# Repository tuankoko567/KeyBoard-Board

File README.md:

# KeyBoard-Board
 A fully custom 4 layers mechanical keyboard PCB based on the RP2040 microcontroller

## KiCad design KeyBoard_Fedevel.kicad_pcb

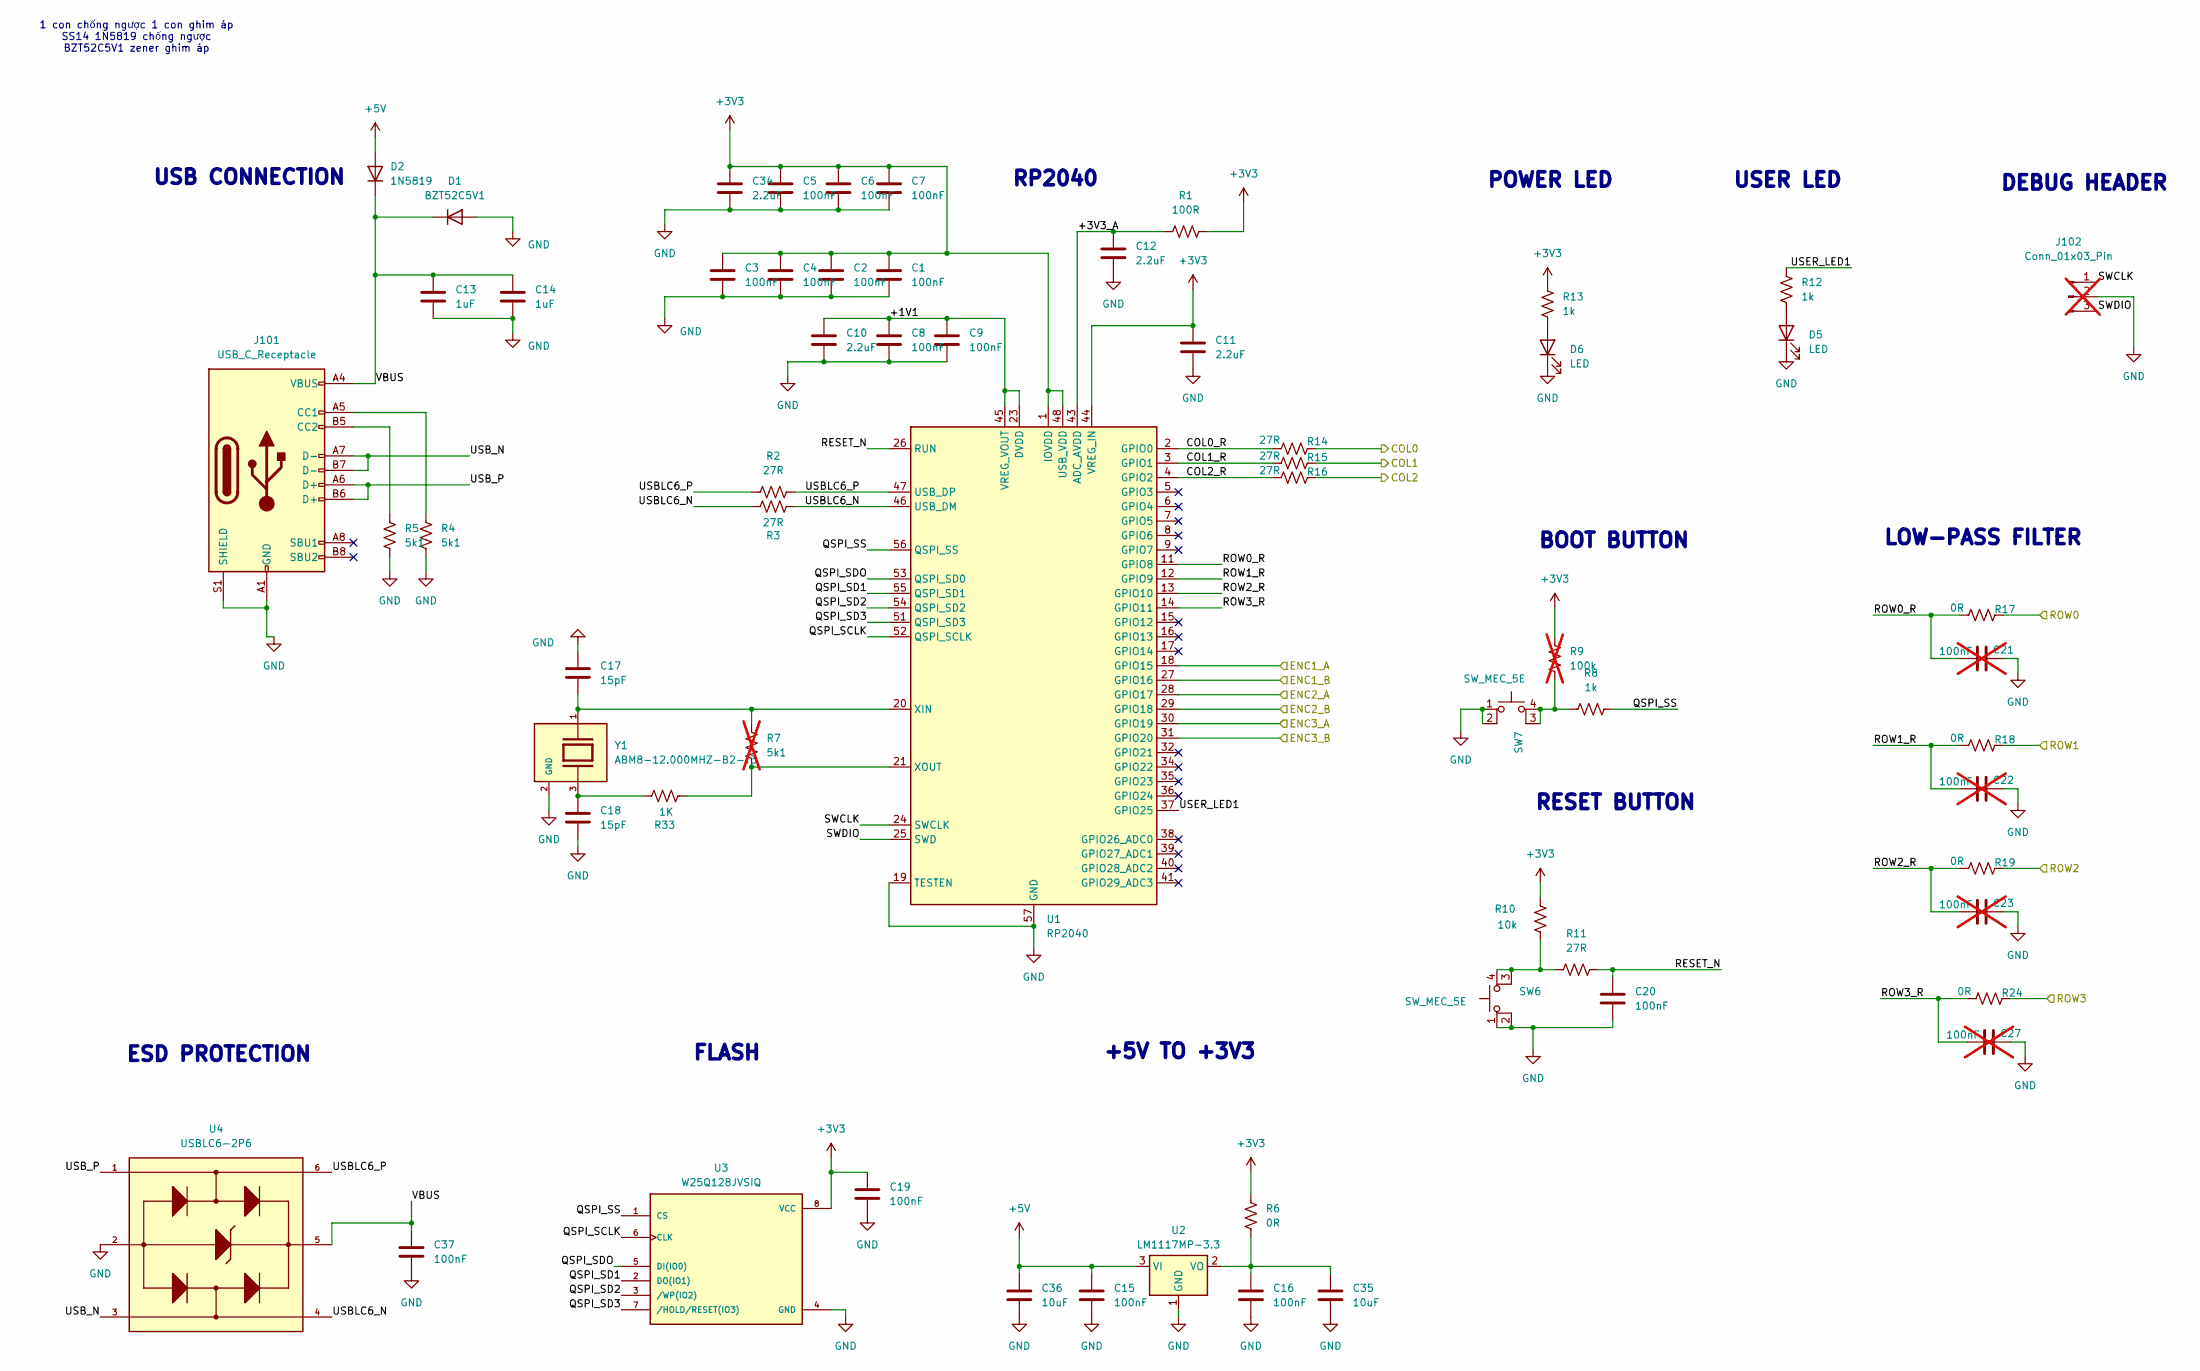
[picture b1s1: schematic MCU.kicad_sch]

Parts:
C1, C2, C3, C4, C5, C6, C7, C8, C9, C15, C16, C19, C20, C37: 100nF; C_0603
C10, C11, C12, C34: 2.2uF; C_0603
C13, C14: 1uF; C_0603
C17, C18: 15pF; C_0603
C21, C22, C23, C27: 100nF; C_0603; not fitted
C35, C36: 10uF; C_0603
D1: BZT52C5V1; Package-Diode-D_SOD_123
D2: 1N5819; D_SMA
D5, D6: LED; LED_0805
J101: USB_C_Receptacle; USB_C_Receptacle_XKB_U262-16XN-4BVC11
J102: Conn_01x03_Pin; PinHeader_1x03_P2.54mm_Vertical; not fitted
R1: 100R; R_0603
R2, R3, R11, R14, R15, R16: 27R; R_0603
R4, R5: 5k1; R_0603
R6, R17, R18, R19, R24: 0R; R_0603
R7: 5k1; R_0603; not fitted
R8, R12, R13: 1k; R_0603
R9: 100k; R_0603; not fitted
R10: 10k; R_0603
R33: 1K; R_0603
SW6, SW7: SW_MEC_5E; SW_SWT0315-050025GSA_REVA
U1: RP2040; QFN-56-1EP_7x7mm_P0.4mm_EP3.2x3.2mm
U2: LM1117MP-3.3; SOT-223-3_TabPin2
U3: W25Q128JVSIQ; SOIC127P790X216-8N; PARTREV I
U4: USBLC6-2P6; SOT-563
Y1: ABM8-12.000MHZ-B2-T3; XTAL_ABM8-12.000MHZ-B2-T3; PARTREV 44041

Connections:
+3V3: C1.2, C2.2, C3.2, C4.2, C5.2, C6.2, C7.2, C11.2, C19.1, C34.2, R1.2, R6.1, R9.2, R10.2, R13.2, U1.1 (IOVDD), U1.10 (IOVDD), U1.22 (IOVDD), U1.33 (IOVDD), U1.42 (IOVDD), U1.44 (VREG_IN), U1.48 (USB_VDD), U1.49 (IOVDD), U3.8 (VCC); also elsewhere on the board
+5V: C15.2, C36.2, D2.2 (A), U2.3 (VI)
/MCU/+1V1: C8.2, C9.2, C10.2, U1.23 (DVDD), U1.45 (VREG_VOUT), U1.50 (DVDD)
/MCU/+3V3_A: C12.2, R1.1, U1.43 (ADC_AVDD)
/MCU/COL0_R: R14.1, U1.2 (GPIO0)
/MCU/COL1_R: R15.1, U1.3 (GPIO1)
/MCU/COL2_R: R16.1, U1.4 (GPIO2)
/MCU/ENC1_A: U1.18 (GPIO15); also elsewhere on the board
/MCU/ENC1_B: U1.27 (GPIO16); also elsewhere on the board
/MCU/ENC2_A: U1.28 (GPIO17); also elsewhere on the board
/MCU/ENC2_B: U1.29 (GPIO18); also elsewhere on the board
/MCU/ENC3_A: U1.30 (GPIO19); also elsewhere on the board
/MCU/ENC3_B: U1.31 (GPIO20); also elsewhere on the board
/MCU/QSPI_SCLK: U1.52 (QSPI_SCLK), U3.6 (CLK)
/MCU/QSPI_SD1: U1.55 (QSPI_SD1), U3.2 (DO(IO1))
/MCU/QSPI_SD2: U1.54 (QSPI_SD2), U3.3 (/WP(IO2))
/MCU/QSPI_SD3: U1.51 (QSPI_SD3), U3.7 (/HOLD/RESET(IO3))
/MCU/QSPI_SDO: U1.53 (QSPI_SD0), U3.5 (DI(IO0))
/MCU/QSPI_SS: R8.2, U1.56 (QSPI_SS), U3.1 (CS)
/MCU/RESET_N: C20.2, R11.2, U1.26 (RUN)
/MCU/ROW0: R17.2; also elsewhere on the board
/MCU/ROW0_R: C21.2, R17.1, U1.11 (GPIO8)
/MCU/ROW1: R18.2; also elsewhere on the board
/MCU/ROW1_R: C22.2, R18.1, U1.12 (GPIO9)
/MCU/ROW2: R19.2; also elsewhere on the board
/MCU/ROW2_R: C23.2, R19.1, U1.13 (GPIO10)
/MCU/ROW3: R24.2; also elsewhere on the board
/MCU/ROW3_R: C27.2, R24.1, U1.14 (GPIO11)
/MCU/SWCLK: J102.1, U1.24 (SWCLK)
/MCU/SWDIO: J102.3, U1.25 (SWD)
/MCU/USBLC6_N: R3.1, R3.2, U1.46 (USB_DM), U4.4
/MCU/USBLC6_P: R2.1, R2.2, U1.47 (USB_DP), U4.6
/MCU/USB_N: J101.A7 (D-), J101.B7 (D-), U4.3
/MCU/USB_P: J101.A6 (D+), J101.B6 (D+), U4.1
/MCU/USER_LED1: R12.2, U1.37 (GPIO25)
/MCU/VBUS: C13.1, C14.1, C37.2, D1.1 (K), D2.1 (K), J101.A4 (VBUS), J101.A9 (VBUS), J101.B4 (VBUS), J101.B9 (VBUS), U4.5
/Switch/COL0: R14.2; also elsewhere on the board
/Switch/COL1: R15.2; also elsewhere on the board
/Switch/COL2: R16.2; also elsewhere on the board
GND: C1.1, C2.1, C3.1, C4.1, C5.1, C6.1, C7.1, C8.1, C9.1, C10.1, C11.1, C12.1, C13.2, C14.2, C15.1, C16.1, C17.2, C18.1, C19.2, C20.1, C21.1, C22.1, C23.1, C27.1, C34.1, C35.1, C36.1, C37.1, D1.2 (A), D5.1 (K), D6.1 (K), J101.A1 (GND), J101.A12 (GND), J101.B1 (GND), J101.B12 (GND), J101.S1 (SHIELD), J102.2, R4.1, R5.1, SW6.1, SW6.2, SW7.1, SW7.2, U1.19 (TESTEN), U1.57 (GND), U2.1 (GND), U3.4 (GND), U4.2, Y1.2 (GND), Y1.4 (GND); also elsewhere on the board
unnamed: C18.2, R33.1, Y1.3
unnamed 44: D5.2 (A), R12.1; also elsewhere on the board
unnamed 45: D6.2 (A), R13.1; also elsewhere on the board
unnamed: J101.A5 (CC1), R4.2
unnamed: J101.B5 (CC2), R5.2
unnamed: R10.1, R11.1, SW6.3 (K), SW6.4 (A)
unnamed: R8.1, R9.1, SW7.3 (K), SW7.4 (A)
unnamed: C17.1, R7.2, U1.20 (XIN), Y1.1
unnamed: R7.1, R33.2, U1.21 (XOUT)
unnamed: C16.2, C35.2, R6.2, U2.2 (VO)

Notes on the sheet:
+5V TO +3V3
RESET BUTTON
POWER LED
USB CONNECTION
RP2040
ESD PROTECTION
LOW-PASS FILTER
USER LED
DEBUG HEADER
FLASH
BOOT BUTTON
1 con chống ngược 1 con ghim áp SS14 1N5819 chống ngược BZT52C5V1 zener ghim áp

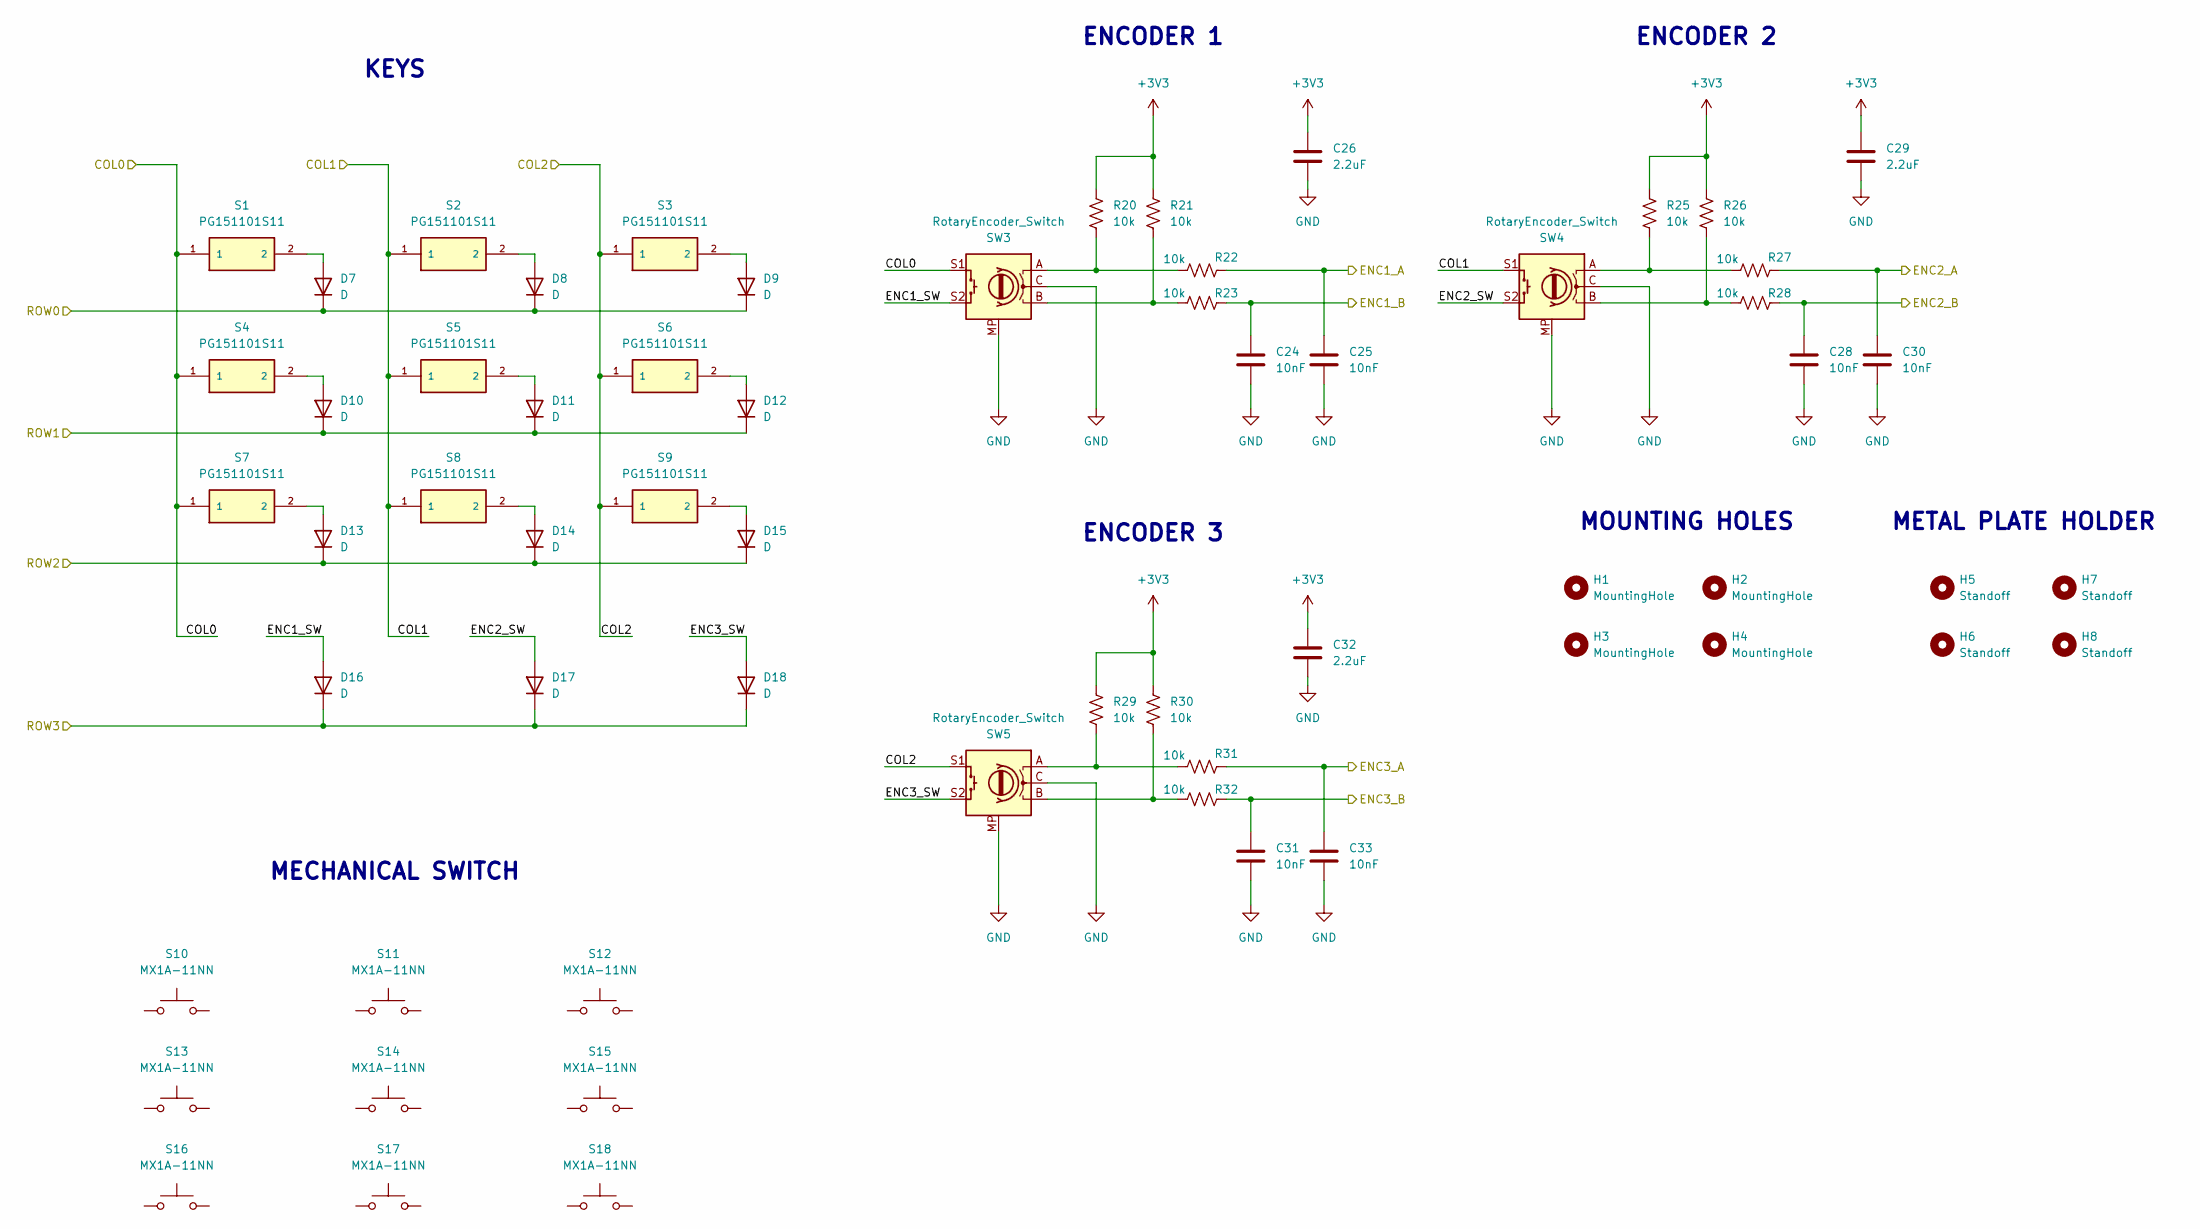
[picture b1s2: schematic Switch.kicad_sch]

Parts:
C24, C25, C28, C30, C31, C33: 10nF; C_0603
C26, C29, C32: 2.2uF; C_0603
D7, D8, D9, D10, D11, D12, D13, D14, D15, D16, D17, D18: D; Package-Diode-D_SOD_123
H1, H2, H3, H4: MountingHole; MH_7.5x3.2mm_RF
H5, H6, H7, H8: Standoff; standoff_9774035151R_M2.5
R20, R21, R22, R23, R25, R26, R27, R28, R29, R30, R31, R32: 10k; R_0603
S1, S2, S3, S4, S5, S6, S7, S8, S9: PG151101S11; SW_PG151101S11; PARTREV A
S10, S11, S12, S13, S14, S15, S16, S17, S18: MX1A-11NN; SW_MX1A-11NN
SW3, SW4, SW5: RotaryEncoder_Switch; RotaryEncoder-Vert-THT-Alps_EC11E_Switch_H20mm

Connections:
+3V3: C26.1, C29.1, C32.1, R20.1, R21.1, R25.1, R26.1, R29.1, R30.1; also elsewhere on the board
/MCU/ENC1_A: C25.1, R22.1; also elsewhere on the board
/MCU/ENC1_B: C24.1, R23.2; also elsewhere on the board
/MCU/ENC2_A: C30.1, R27.1; also elsewhere on the board
/MCU/ENC2_B: C28.1, R28.2; also elsewhere on the board
/MCU/ENC3_A: C33.1, R31.1; also elsewhere on the board
/MCU/ENC3_B: C31.1, R32.2; also elsewhere on the board
/MCU/ROW0: D7.1 (K), D8.1 (K), D9.1 (K); also elsewhere on the board
/MCU/ROW1: D10.1 (K), D11.1 (K), D12.1 (K); also elsewhere on the board
/MCU/ROW2: D13.1 (K), D14.1 (K), D15.1 (K); also elsewhere on the board
/MCU/ROW3: D16.1 (K), D17.1 (K), D18.1 (K); also elsewhere on the board
/Switch/COL0: S1.1, S4.1, S7.1, SW3.S1; also elsewhere on the board
/Switch/COL1: S2.1, S5.1, S8.1, SW4.S1; also elsewhere on the board
/Switch/COL2: S3.1, S6.1, S9.1, SW5.S1; also elsewhere on the board
/Switch/ENC1_SW: D16.2 (A), SW3.S2
/Switch/ENC2_SW: D17.2 (A), SW4.S2
/Switch/ENC3_SW: D18.2 (A), SW5.S2
GND: C24.2, C25.2, C26.2, C28.2, C29.2, C30.2, C31.2, C32.2, C33.2, SW3.C, SW3.MP (Shield), SW4.C, SW4.MP (Shield), SW5.C, SW5.MP (Shield); also elsewhere on the board
unnamed: D7.2 (A), S1.2
unnamed: D8.2 (A), S2.2
unnamed: D9.2 (A), S3.2
unnamed: D10.2 (A), S4.2
unnamed: D11.2 (A), S5.2
unnamed: D12.2 (A), S6.2
unnamed: D13.2 (A), S7.2
unnamed: D14.2 (A), S8.2
unnamed: D15.2 (A), S9.2
unnamed: R20.2, R22.2, SW3.A
unnamed: R21.2, R23.1, SW3.B
unnamed: R25.2, R27.2, SW4.A
unnamed: R26.2, R28.1, SW4.B
unnamed: R29.2, R31.2, SW5.A
unnamed: R30.2, R32.1, SW5.B

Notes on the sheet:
ENCODER 2
ENCODER 1
METAL PLATE HOLDER
ENCODER 3
MOUNTING HOLES
KEYS
MECHANICAL SWITCH

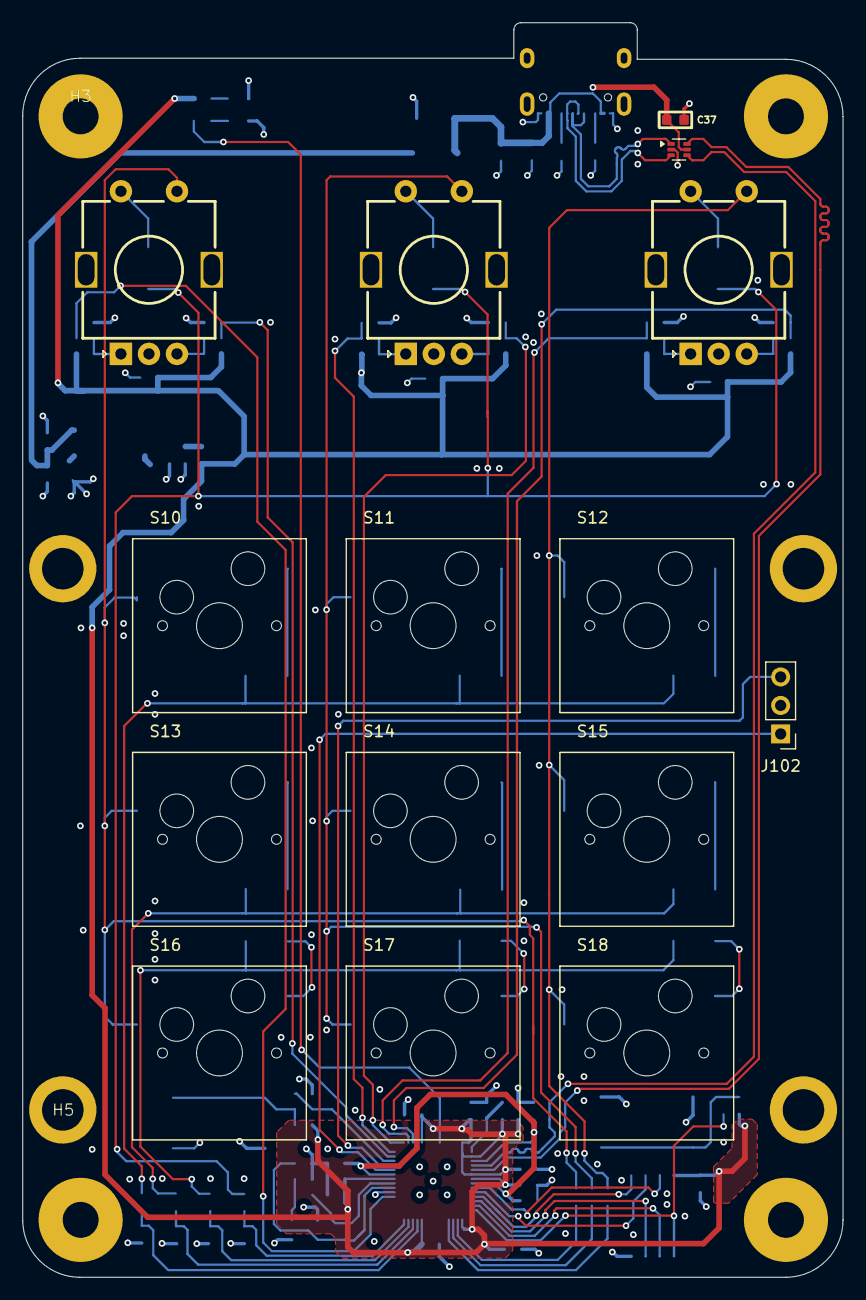
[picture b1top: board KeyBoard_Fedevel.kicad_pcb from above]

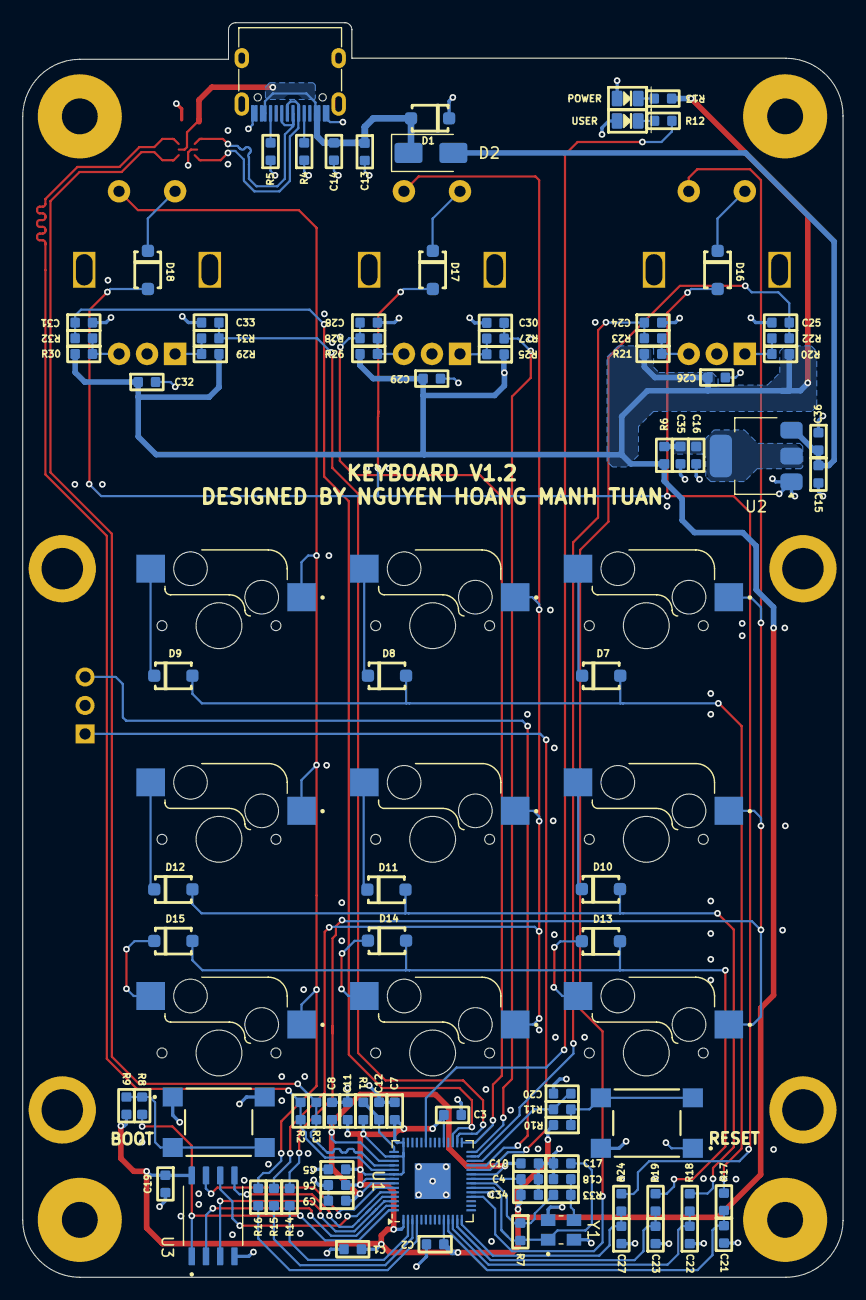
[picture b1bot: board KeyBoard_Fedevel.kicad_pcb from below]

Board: 4 copper layers, 73.1 x 111.9 mm, 124 parts (101 on the bottom side), 68 nets.

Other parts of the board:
POWER: LED; LED_0805
USER: LED; LED_0805

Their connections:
GND: POWER.1 (K), USER.1 (K); also elsewhere on the board
unnamed 44: USER.2 (A); also elsewhere on the board
unnamed 45: POWER.2 (A); also elsewhere on the board
